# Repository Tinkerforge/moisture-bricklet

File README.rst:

Moisture Bricklet
=================

This repository contains the firmware source code and the hardware design
files. The documentation generator configs can be found at
https://github.com/Tinkerforge/generators

Repository Content
------------------

software/:
 * examples/: Examples for all supported languages
 * build/: Compiled files
 * src/: Source code of firmware
 * Makefile: Makefile to build project

hardware/:
 * Contains KiCad project files and additionally schematics as PDF

datasheets/:
 * Contains datasheets for sensors and complex ICs that are used

Hardware
--------

The hardware is designed with the open source EDA Suite KiCad
(http://www.kicad.org). Before you are able to open the files,
you have to install the Tinkerforge kicad-libraries
(https://github.com/Tinkerforge/kicad-libraries). You can either clone
them directly in hardware/ or clone them in a separate folder and
symlink them into hardware/
(ln -s kicad_path/kicad-libraries project_path/hardware). After that you
can open the .pro file in hardware/ with KiCad and from there view and
modify the schematics and the PCB layout.

Software
--------

If you want to do your own Brick/Bricklet firmware development we highly
recommend that you use our build environment setup script and read the
tutorial (https://www.tinkerforge.com/en/doc/Tutorials/Tutorial_Build_Environment/Tutorial.html).

To compile the C code we recommend you to install the newest GNU Arm Embedded
Toolchain (https://launchpad.net/gcc-arm-embedded/+download).
You also need to install bricklib (https://github.com/Tinkerforge/bricklib)
and brickletlib (https://github.com/Tinkerforge/brickletlib).

You can either clone it directly in software/src/ or clone it in a
separate folder and symlink it into software/src/
(ln -s bricklib_path/bricklib project_path/software/src/ and
ln -s brickletlib_path/brickletlib project_path/software/src/).
Finally make sure to have CMake installed
(http://www.cmake.org/cmake/resources/software.html).

After that you can build the firmware by invoking make in software/.
The firmware (.bin) can then be found in software/build/ and uploaded
with brickv (click button "Flashing" on start screen).

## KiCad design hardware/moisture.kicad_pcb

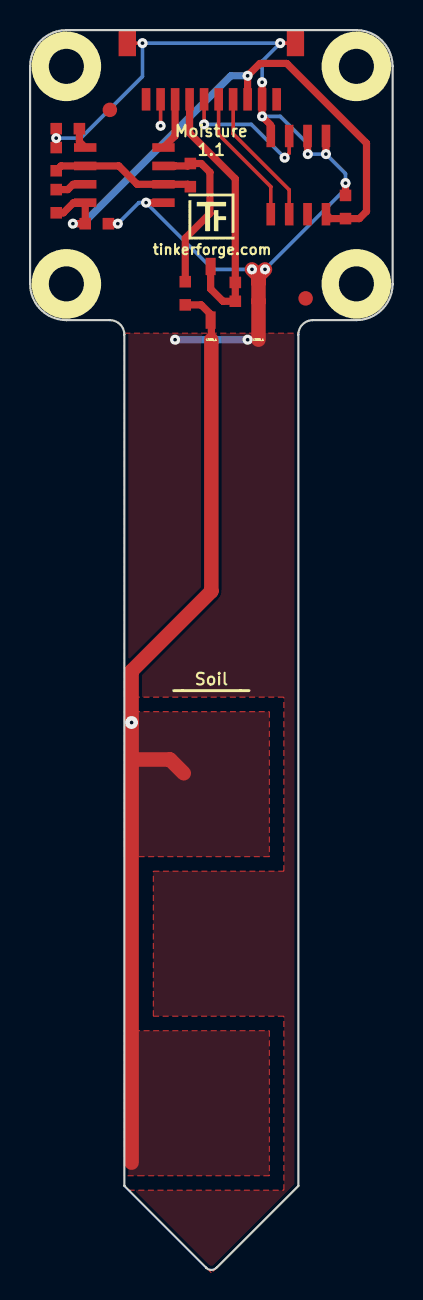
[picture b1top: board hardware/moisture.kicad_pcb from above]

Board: 2 copper layers, 25.0 x 85.5 mm, 23 parts (2 on the bottom side), 12 nets.

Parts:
C1, C4: 100nF; C0603
C2: 1µF; C0603
C3: 100pF; C0603
C5: 10nF; C0603
D1: B0520LW; SOD-123
Fiducial_Mark: VAL**; Fiducial_Mark
Fiducial_Mark#2: VAL**; Fiducial_Mark
P1: CON-SENSOR
P2, P3: CONN_1; con
R1: 470k; R0603
R2: 4k7; R0603
R3: 10k; R0603
R4: 7.5k; R0603
U1: M24C64; SOIC8
U2: ICM7555; SOIC8
U3, U4, U5, U6: DRILL; DRILL_NP
VAL: CE_5mm
VAL#2: WEEE_7mm

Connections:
CLK: R2.1, R4.2, U2.3
GND: C1.2, C2.2, C3.2, C4.1, C5.2, P1.2, P1.9, P1.EP, P3.1, R1.1, U1.1, U1.2, U1.4, U2.1
unnamed: C2.1, D1.2, P1.7, R1.2
unnamed: C3.1, R4.1, U2.2, U2.6
unnamed: C5.1, U2.5
unnamed: D1.1, P2.1, R2.2
unnamed: P1.4, U1.6
unnamed: P1.5, U1.5
unnamed: P1.6, U1.3
unnamed: R3.1, U2.7
RESET: P1.8, U2.4
VCC: C1.1, C4.2, P1.3, R3.2, U1.8, U2.8

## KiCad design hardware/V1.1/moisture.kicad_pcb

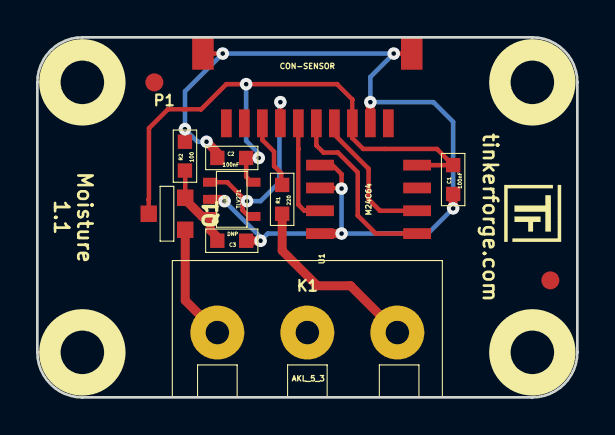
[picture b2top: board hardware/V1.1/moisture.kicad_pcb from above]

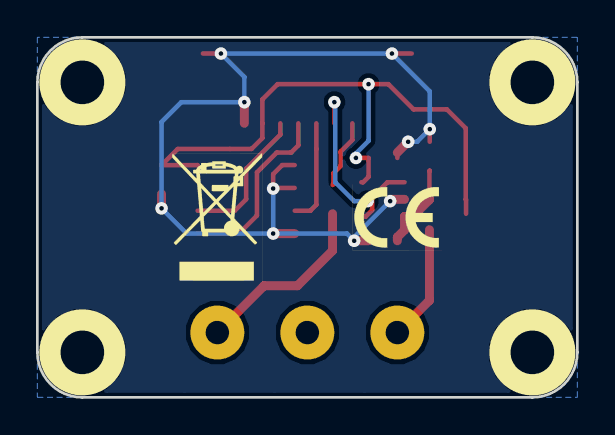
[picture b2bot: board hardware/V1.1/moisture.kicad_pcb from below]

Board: 2 copper layers, 30.0 x 20.0 mm, 18 parts (2 on the bottom side), 10 nets.

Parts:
C1, C2: 100nF; 0603
C3: DNP; 0603
Fiducial_Mark: VAL**; Fiducial_Mark
Fiducial_Mark#2: VAL**; Fiducial_Mark
K1: AKL_5_3
P1: CON-SENSOR
Q1: S9013; SOT23EBC
R1: 220; 0603
R2: 100; 0603
U1: M24C64; SOIC8
U2: TLV271; SOT23-5
U3, U4, U5, U6: DRILL; DRILL_NP
VAL: CE_5mm
VAL#2: WEEE_7mm

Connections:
GND: C1.2, C2.2, C3.2, P1.2, P1.EP, R2.1, U1.1, U1.2, U1.4, U2.2
unnamed: C3.1, Q1.1, R2.2, U2.3
unnamed: K1.1, R1.2
unnamed: K1.3, Q1.2
unnamed: P1.4, U1.6
unnamed: P1.5, U1.5
unnamed: P1.6, U1.3
unnamed: P1.7, U2.1, U2.4
unnamed: P1.8, R1.1
VCC: C1.1, C2.1, P1.3, Q1.3, U1.8, U2.5

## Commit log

2013-07-23 Initial commit for Moisture Bricklet
2013-08-21 windows: Don't trigger a build in generate_makefile.bat
    Also use normal make instead of a special named one.
2013-09-13 Simplify switch
2013-09-13 Add examples for Moisture Bricklet
2013-09-20 vbnet: Fix typo
2013-10-15 add hardware files
2013-11-21 Avoid division by zero in average calculation
2013-11-27 Fix typo
2013-12-19 Fix wrong length for GetDebounce packet (through brickletlib)
2014-01-10 Add Perl examples
2014-01-15 php: Use const for constant values
2014-02-07 Add Mathematica examples
2014-02-10 perl: fixed namespace
2014-02-12 javascript: add examples
2014-02-18 javascript: examples fixed
2014-02-20 javascript: adding html examples
2014-02-20 javascript: adding comment
2014-02-24 javascript: port 4280, startExample()
2014-02-28 javascript: Break long lines and cleanup whitespace
2014-03-05 Add LabVIEW examples
2014-03-06 labview: Add examples in LV2010 format
2014-03-26 matlab: add examples
2014-04-02 java: Unify constants style
2014-04-02 perl: Unify print style
2014-04-17 matlab: Adapt examples to new callback style
2014-04-17 matlab: Add parentheses to make pygments happy
2014-07-15 java: Replace System.console() usage with an Eclipse compatible pattern
2014-12-02 Use ReadLine instead of ReadKey for C# example
2015-02-13 vbnet: Use ReadLine instead of ReadKey
    Because ReadKey doesn't work with a pipe as stdin on the RED Brick.
2015-03-02 windows: Stop cmake from searching for mingw32-make.exe
    Using MinGW Makefiles as generator makes cmake search for mingw32-make.exe
    which might not be installed because GnuWin32's make.exe is used instead.
2015-03-25 Change from -O3 to -O2 because -O3 produces broken code with GCC 4.8.1
2015-03-26 checkin of prototype files
2015-03-31 two new prototypes for moisture bricklet (oportunities)
2015-04-02 add fiducials
2015-04-02 change labels, drc
2015-04-07 remove wrong masks
2015-04-09 c: Whitespace
2015-04-24 adapt values, change to astable operation (figure 1a in icm7555 datasheet)
2015-04-24 drc executed
2015-04-24 fix logo position
2015-05-04 connect pin3 to ground
2015-06-24 javascript: Clean up output creation
2015-06-24 java: Remove unnecessary parentheses
2015-07-25 Make JavaScript browser example textarea readonly
2015-07-27 Cleanup C/C++, C#, Java, Python and Ruby examples
2015-07-29 Reformat changelog
2015-08-01 remove not used prototypes, move to new hardware version
2015-08-03 update schematic
2015-08-07 Use full device class name in Python examples
2015-08-12 Fix minor warnings in C/C++ examples
2015-08-13 Use correct simple value type
2015-08-14 Cleanup Delphi examples
2015-08-18 Cleanup VB.NET examples
2015-08-19 Cleanup Perl examples
2015-08-21 Use shorter print statement in Perl example
2015-09-09 Duplicate cmake call to fix bug during cmake creation
2015-09-30 Generator based example cleanup
2015-11-12 matlab: Fix callback handling for R2014a
    http://undocumentedmatlab.com/blog/matlab-callbacks-for-java-events-in-r2014a
2015-11-25 Include date and commit into changelog
2016-05-18 c: Add missing device destroy call
2016-07-01 Make the change UID comment more explicit
2017-04-13 csharp: Adapt example
2017-04-21 shell: Adapt example
2017-06-02 octave: Use javaObject instead of deprecated java_new
2017-08-01 Add 3d information (final)
2017-08-01 Add 3d model (*.step & *.FCStd)
2017-11-30 Update examples from generator
2017-12-07 mathematica: Also generate .nb files
2018-01-26 c: Fine-tune printf format
2018-02-19 javascript: Close div tag correctly
2018-02-20 Cleanup KiCad libraries config
    Ensure LibDir=kicad-libraries and LibName1=tinkerforge.
    Remove special library.
2018-05-24 perl: Use strict in examples
2018-07-11 Add Makefile with docker support
2018-07-11 Remove obsolete generate_makefile scripts
2018-07-11 Update directory structure and build instructions
2018-09-14 vbnet: Fix typo in comment
2018-11-06 Add rust examples
2018-11-07 rust: Accept host names for ip connection, fix naming inconsistencies
2018-11-07 rust: Rename callback receivers.
2018-12-14 Add go examples.
2018-12-18 go: Change import path.
2018-12-18 go: Change import path again.
2018-12-20 rust: Reformat examples.
2019-01-24 mqtt: Add examples.
2019-01-24 mqtt: Fix example header.
2019-01-24 mqtt: Remove executable bit in example permissions.
2019-01-24 go: Minor example fixes.
2019-01-24 mqtt: Minor example fixes.
2019-03-28 mqtt: Fix whitespace.
2019-08-22 c: Adapt to bindings changes
2020-01-13 examples: Use python3 input instead of python2 raw_input.
2020-01-13 examples: mqtt: Remove trailing whitespace.
2021-10-25 Update KiCad link
    https://www.kicad.org/blog/2021/10/Avoid-links-to-former-kicad-domain/
2022-05-10 go: Fix format string
2022-07-06 Add license files.

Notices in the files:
hardware/V1.1/moisture.kicad_pcb:
Copyright Tinkerforge GmbH 2013.
This documentation describes Open Hardware and is licensed under the
CERN OHL v. 1.1.
hardware/moisture.kicad_pcb:
Licensed under CERN OHL v.1.1
Copyright (©) 2014, B.Nordmeyer
Copyright Tinkerforge GmbH 2014.
